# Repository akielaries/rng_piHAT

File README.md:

# rng_piHAT
Pi HAT with randon noise and number generators 

# Design
## PCB

Prototype PCB designs I'm playing around with

## Schematic

# Hardware Random Number Generators
## Some notes for potential use
Potential entropy sources (with a combination of other parts):
* one of the many amps or comparators I have
* PC817 optocoupler
* CD4047 CMOS monostable/astable multivibrator
* NE555 timer
* PT2399 digital delay echo audio processor
* Linear Feedback Shift Register

## Avalanche noise generator
The avalanche noise generator circuit consists of:
- 2x 4.7k resistors
- 1x 10k resistor
- 1x 1m resistor
- 3x 3904 NPN transistors
- 10uf capacitor
- 0.1uf capacitor

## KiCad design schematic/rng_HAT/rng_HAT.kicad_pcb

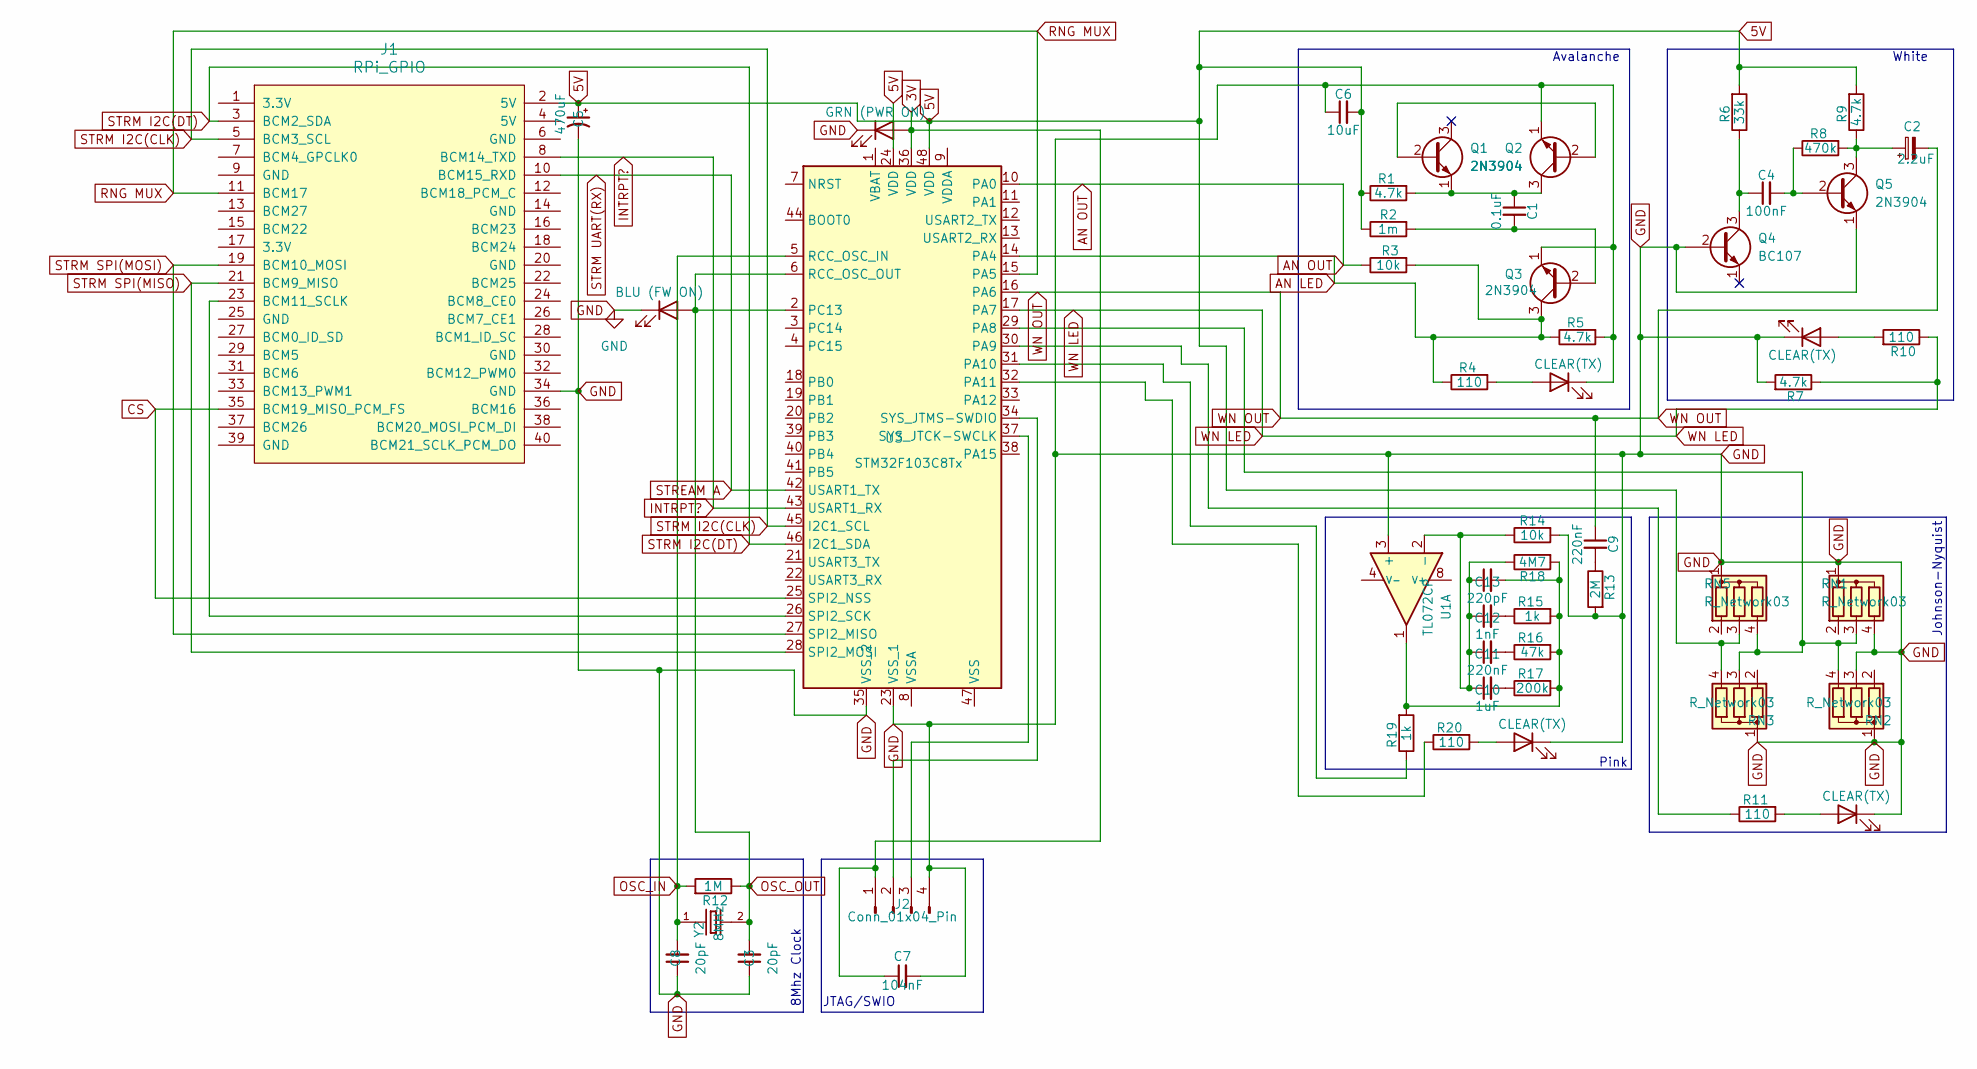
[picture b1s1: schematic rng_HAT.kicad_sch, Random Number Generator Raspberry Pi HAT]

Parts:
C1: 0.1uF; C_0603_1608Metric_Pad1.08x0.95mm_HandSolder
C2: 2.2uF; C_0603_1608Metric_Pad1.08x0.95mm_HandSolder
C3, C8: 20pF; C_0603_1608Metric_Pad1.08x0.95mm_HandSolder
C4: 100nF; C_0603_1608Metric_Pad1.08x0.95mm_HandSolder
C5: 470uF; CP_Elec_3x5.3
C6: 10uF; C_0603_1608Metric_Pad1.08x0.95mm_HandSolder
C7: 104nF; C_0603_1608Metric_Pad1.08x0.95mm_HandSolder
C9, C11: 220nF; C_0603_1608Metric_Pad1.08x0.95mm_HandSolder
C10: 1uF; C_0603_1608Metric_Pad1.08x0.95mm_HandSolder
C12: 1nF; C_0603_1608Metric_Pad1.08x0.95mm_HandSolder
C13: 220pF; C_0603_1608Metric_Pad1.08x0.95mm_HandSolder
D1: BLU (FW ON); LED_0201_0603Metric
D2, D3, D5, D6: CLEAR(TX); LED_0201_0603Metric
D4: GRN (PWR ON); LED_0201_0603Metric
J1: RPi_GPIO; RPI_Hat_B+
J2: Conn_01x04_Pin; PinHeader_1x04_P1.00mm_Horizontal
Q1, Q2, Q3, Q5: 2N3904; TO-92_Inline
Q4: BC107; TO-18-3
R1, R5, R7, R9: 4.7k; R_0201_0603Metric
R2: 1m; R_0201_0603Metric
R3, R14: 10k; R_0201_0603Metric
R4, R10, R11, R20: 110; R_0201_0603Metric
R6: 33k; R_0201_0603Metric
R8: 470k; R_0201_0603Metric
R12: 1M; R_0201_0603Metric
R13: 2M; R_0201_0603Metric
R15, R19: 1k; R_0201_0603Metric
R16: 47k; R_0201_0603Metric
R17: 200k; R_0201_0603Metric
R18: 4M7; R_0201_0603Metric
RN1, RN2, RN3, RN5: R_Network03; R_Array_SIP4
U1: TL072CP; DIP-8_W7.62mm_LongPads
U3: STM32F103C8Tx; LQFP-48_7x7mm_P0.5mm
Y2: 8MHz; Crystal_SMD_3215-2Pin_3.2x1.5mm

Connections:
3V: C7.1, D4.2 (A), J2.1, U3.36 (VDD)
5V: C5.1, C6.2, J1.2 (5V), R1.1, R2.1, R6.2, R9.2, RN3.4 (R3), RN5.3 (R2), U3.24 (VDD), U3.48 (VDD)
AN LED: Q3.3 (C), R3.2, R4.1, R5.1, U3.14 (PA4)
AN OUT: R3.1, U3.10 (PA0)
CS: J1.35 (BCM19_MISO_PCM_FS), U3.25 (SPI2_NSS)
GND: C3.1, C5.2, C6.1, C7.2, C8.1, D1.1 (K), D2.1 (K), D3.1 (K), D4.1 (K), D5.1 (K), D6.1 (K), J1.34 (GND), J2.4, Q2.1 (E), Q3.1 (E), Q4.2 (B), Q5.1 (E), R5.2, R7.2, R13.2, R14.2, RN1.1 (common), RN1.4 (R3), RN2.1 (common), RN2.3 (R2), RN3.1 (common), RN5.1 (common), U1.3 (+), U3.23 (VSS_1), U3.35 (VSS_2)
INTRPT?: J1.8 (BCM14_TXD), U3.43 (USART1_RX)
unnamed: C9.2, R13.1
unnamed: C10.2, R17.1
unnamed: C11.2, R16.1
unnamed: C12.2, R15.1
unnamed: C13.2, R15.2, R16.2, R17.2, R18.2, R19.2, U1.1
unnamed: D2.2 (A), R4.2
unnamed: D3.2 (A), R10.2
unnamed: D5.2 (A), R11.2
unnamed: D6.2 (A), R20.2
unnamed: J1.23 (BCM11_SCLK), U3.26 (SPI2_SCK)
unnamed: J2.2, U3.34 (SYS_JTMS-SWDIO)
unnamed: J2.3, U3.37 (SYS_JTCK-SWCLK)
unnamed: Q1.2 (B), Q2.2 (B)
unnamed: C1.1, Q1.1 (E), Q2.3 (C), R1.2
unnamed: C1.2, Q3.2 (B), R2.2
unnamed: C4.1, Q4.3 (C), R6.1
unnamed: C4.2, Q5.2 (B), R8.1
unnamed: C2.1, Q5.3 (C), R8.2, R9.1
unnamed: RN1.3 (R2), RN2.4 (R3), RN3.3 (R2), RN5.4 (R3), U3.29 (PA8)
unnamed: C10.1, C11.1, C12.1, C13.1, R14.1, R18.1, U1.2 (-)
unnamed: R11.1, U3.30 (PA9)
unnamed: R19.1, U3.31 (PA10)
unnamed: R20.1, U3.32 (PA11)
unnamed: C8.2, R12.2, U3.5 (RCC_OSC_IN), Y2.1
RNG MUX: J1.11 (BCM17), U3.15 (PA5)
STREAM A: J1.10 (BCM15_RXD), U3.42 (USART1_TX)
STRM I2C(CLK): J1.5 (BCM3_SCL), U3.45 (I2C1_SCL)
STRM I2C(DT): J1.3 (BCM2_SDA), U3.46 (I2C1_SDA)
STRM SPI(MISO): J1.21 (BCM9_MISO), U3.28 (SPI2_MOSI)
STRM SPI(MOSI): J1.19 (BCM10_MOSI), U3.27 (SPI2_MISO)
WN LED: R7.1, R10.1, U3.17 (PA7)
WN OUT: C2.2, C9.1, U3.16 (PA6)

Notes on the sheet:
White
Avalanche
Johnson-Nyquist
Pink
JTAG/SWIO
8Mhz Clock

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
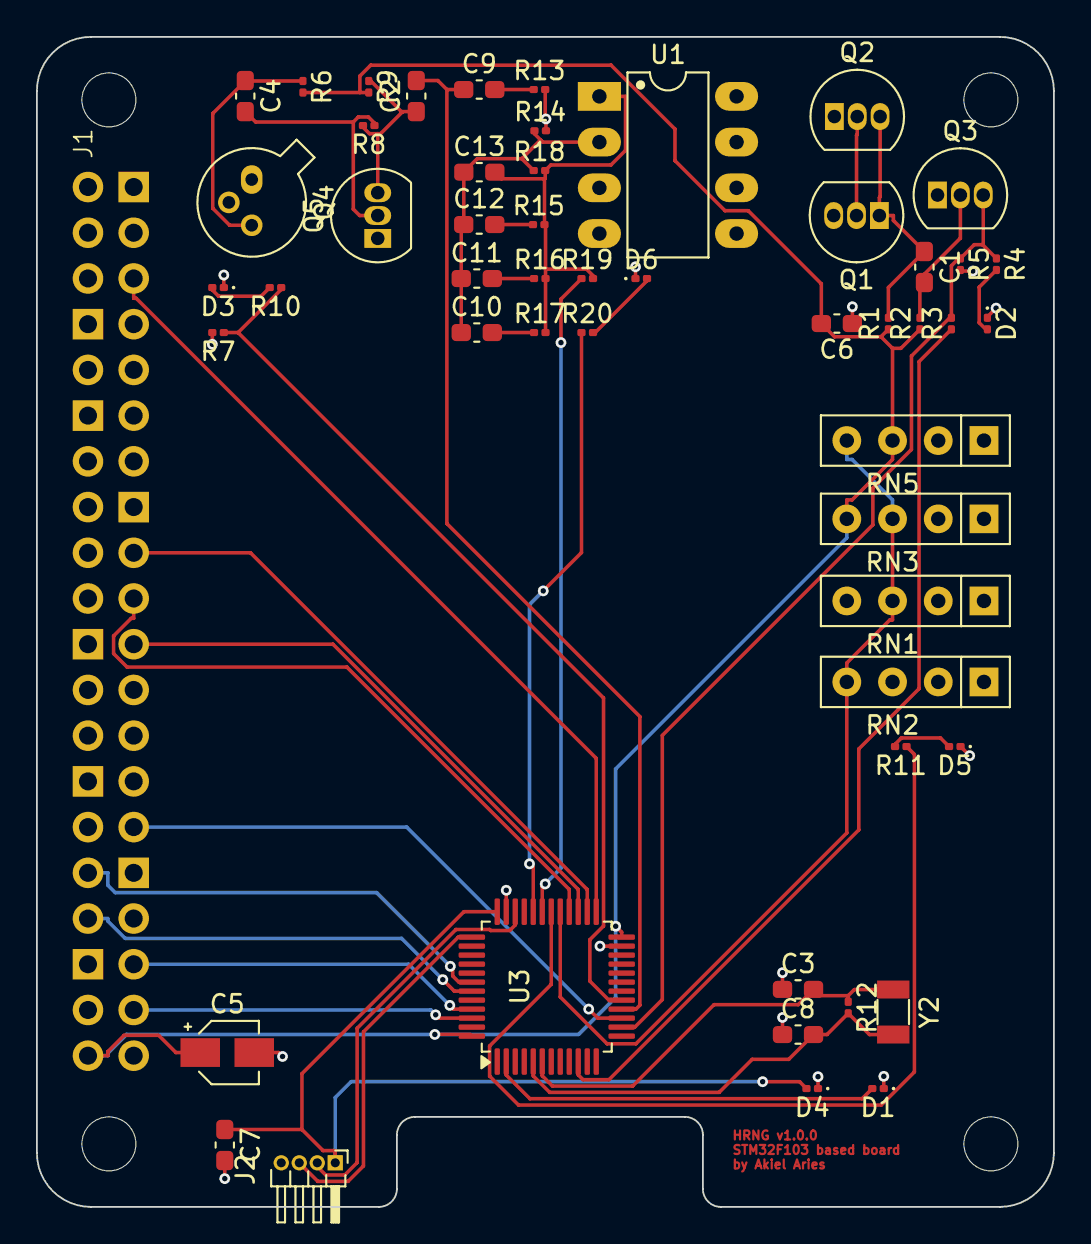
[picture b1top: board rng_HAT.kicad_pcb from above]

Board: 2 copper layers, 56.5 x 65.0 mm, 53 parts (0 on the bottom side), 41 nets.

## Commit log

2024-10-12 adding some stubs
2024-10-13 comms interface. will start with UART and figure out SPI along the wayu
2024-10-13 avalanche noise generator RNG stubs
2024-10-13 adding analog comms file stub
2024-10-13 updating comms interface
2024-10-13 no need for a driver implementation
2024-10-13 updating driver comments
2024-10-13 adding SPI and UART file stubs
2024-10-13 moving comms to a dir
2024-10-13 driver interface updates, lazy makefile
2024-10-13 updates, NULL in stddef?? ...
2024-10-13 stddef
2024-10-13 should probably add ci checks early on, this will be a neat project
2024-10-13 updating comms stubs
2024-10-13 updating rng circuit driver stubs
2024-10-13 adding some flags for debugging, updating uart driver stub
2024-10-13 updating uart stubs
2024-10-13 SPI and I2C stubs
2024-10-13 updating makefile
2024-10-13 adding analog comms as a type
2024-10-13 updating comms comments
2024-10-13 updating comments
2024-10-13 format
2024-10-13 adding schematic from other PI HAT
2024-10-13 stubbing out main, getting components working before touching hardware...
2024-10-13 updating schematic
2024-10-13 updating comms
2024-10-13 removing bin
2024-10-13 updating shematic
2024-10-14 updates to makefile
2024-10-14 updating main
2024-10-14 adding device registry
2024-10-14 update comms
2024-10-14 updates to rng and device reg
2024-10-14 adding debug prints
2024-10-19 updating stuff
2024-10-20 playing with dieharder
2024-10-27 some stuff
2024-10-27 adding HAT submodule
2024-10-27 schematic updates
2024-10-27 working PCB?
2024-10-27 different layer for serial lines and analog lines?
2024-10-28 very broken! reverting and redoing
2024-10-28 working again. small changes
2024-10-28 adding and running tests
2024-10-28 reverting and starting over PCB. no routes
2024-10-28 updates?
2024-10-28 some more PCB updates
2024-10-28 updating schematic with white noise filter. no output stage? useful? need to test some of these components....
2024-10-28 PCB updates. holding off on routes for now
2024-10-28 PCB with traces. 2 errors, mostly warnings for cutoffs
2024-10-28 addressing some DRC warnings
2024-10-29 uhhh restarting traces and vias
2024-10-29 pics and readme?
2024-10-29 readme
2024-10-29 images look broken. too lazy to fix
2024-10-29 PDFs but too lazy to make images out of these rn. maybe when its finished?
